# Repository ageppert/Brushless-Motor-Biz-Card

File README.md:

# Brushless-Motor-Biz-Card
Wind your own brushless motor and experiment in the form factor of a business card!

Follow this project at: https://hackaday.io/project/196576-brushless-motor-and-driver-business-card-kit

# Hardware Version History (latest on top)

HWV0.1 - Prototypes

# REFERENCES

Carl Bugeja - PCB Motors and related magical creations

https://www.youtube.com/@CarlBugeja

Random Access Projects - Open loop brushless motor and beyond

https://www.youtube.com/channel/UCRd9x4pmbc09_RXTrkSY2Gg

Electronoobs - brushless motor and ESC projects

https://www.youtube.com/@ELECTRONOOBS

SimpleFOC Project

https://simplefoc.com/

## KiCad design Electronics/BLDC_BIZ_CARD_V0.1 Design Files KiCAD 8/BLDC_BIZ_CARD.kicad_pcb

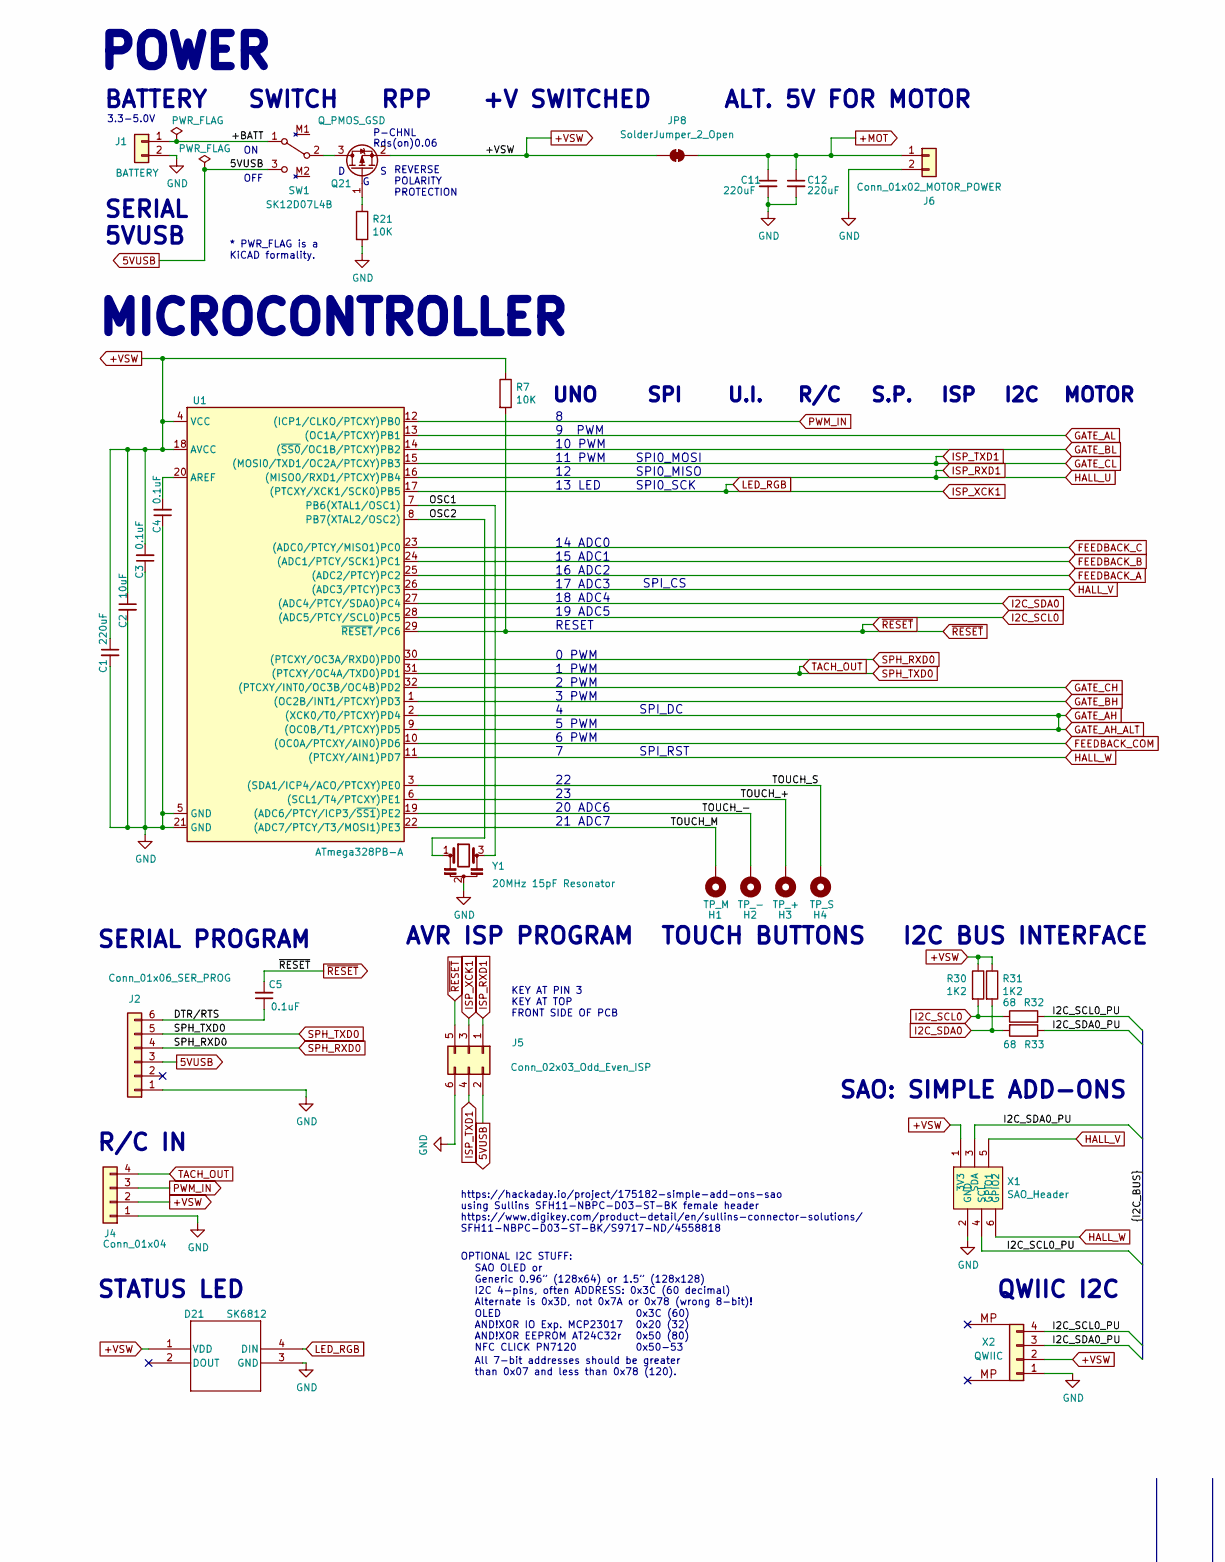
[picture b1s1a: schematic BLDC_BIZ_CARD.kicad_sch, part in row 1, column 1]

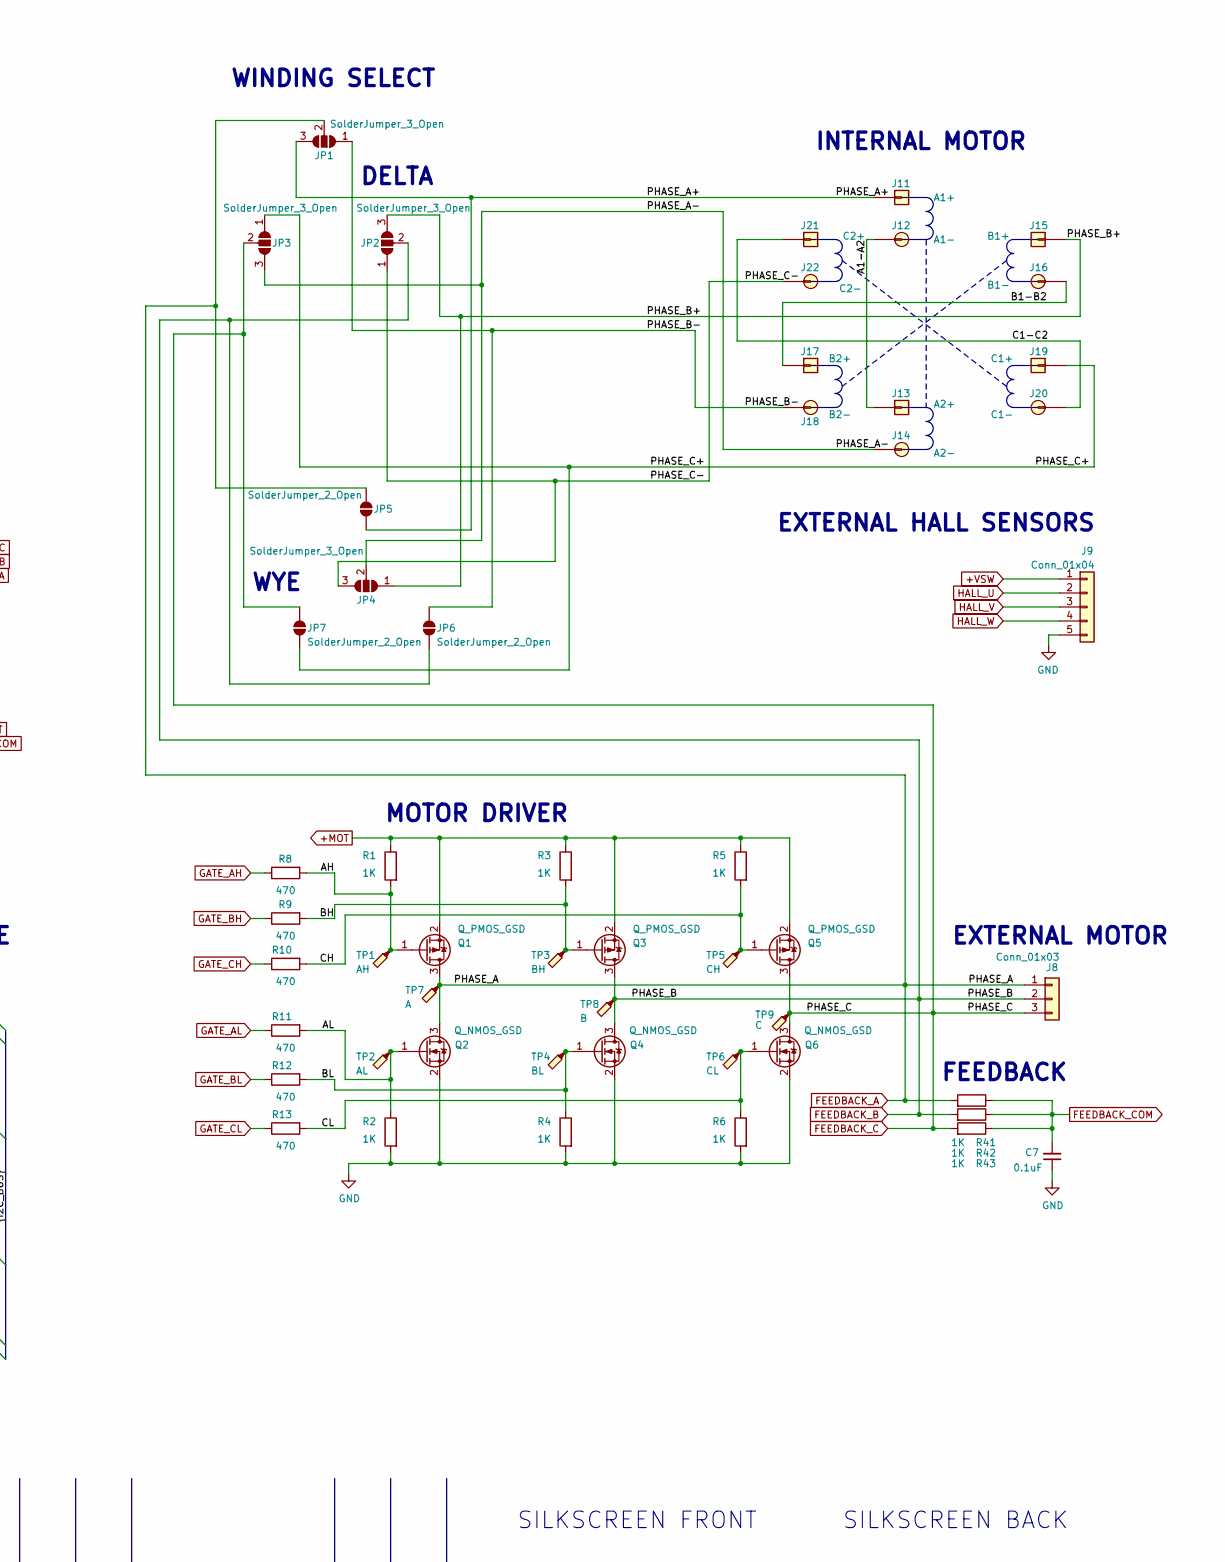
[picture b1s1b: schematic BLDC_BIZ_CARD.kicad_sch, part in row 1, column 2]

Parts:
C1, C11, C12: 220uF; C_1206_3216Metric; LCSC C412252
C2: 10uF; C_0805_2012Metric; LCSC C17024
C3, C4, C5, C7: 0.1uF; C_0805_2012Metric; LCSC C28233
D21: SK6812; 4960_ADA_REV_RGB_LED_short_pads; MPN SK6812-E; Digi-Key_PN 1528-4960-ND
H1: TP_M; BIZ_CARD_TOUCH_PAD
H2: TP_-; BIZ_CARD_TOUCH_PAD
H3: TP_+; BIZ_CARD_TOUCH_PAD
H4: TP_S; BIZ_CARD_TOUCH_PAD
J1: BATTERY; PinSocket_1x02_P2.54mm_Vertical
J2: Conn_01x06_SER_PROG; PinSocket_1x06_P2.54mm_Vertical
J4: Conn_01x04; PinSocket_1x04_P2.54mm_Vertical
J5: Conn_02x03_Odd_Even_ISP; PinSocket_2x03_P2.54mm_Vertical
J6: Conn_01x02_MOTOR_POWER; PinSocket_1x02_P2.54mm_Vertical
J8: Conn_01x03; PinSocket_1x03_P2.54mm_Vertical
J9: Conn_01x04; PinSocket_1x05_P2.54mm_Vertical
J11: A1+; TestPoint_THTPad_1.0x1.0mm_Drill0.5mm
J12: A1-; TestPoint_THTPad_D1.0mm_Drill0.5mm
J13: A2+; TestPoint_THTPad_1.0x1.0mm_Drill0.5mm
J14: A2-; TestPoint_THTPad_D1.0mm_Drill0.5mm
J15: B1+; TestPoint_THTPad_1.0x1.0mm_Drill0.5mm
J16: B1-; TestPoint_THTPad_D1.0mm_Drill0.5mm
J17: B2+; TestPoint_THTPad_1.0x1.0mm_Drill0.5mm
J18: B2-; TestPoint_THTPad_D1.0mm_Drill0.5mm
J19: C1+; TestPoint_THTPad_1.0x1.0mm_Drill0.5mm
J20: C1-; TestPoint_THTPad_D1.0mm_Drill0.5mm
J21: C2+; TestPoint_THTPad_1.0x1.0mm_Drill0.5mm
J22: C2-; TestPoint_THTPad_D1.0mm_Drill0.5mm
JP1, JP2, JP3, JP4: SolderJumper_3_Open; SolderJumper-3_P1.3mm_Open_RoundedPad1.0x1.5mm_NumberLabels
JP5, JP6, JP7, JP8: SolderJumper_2_Open; SolderJumper-2_P1.3mm_Open_RoundedPad1.0x1.5mm
Q1, Q3, Q5: Q_PMOS_GSD; SOT-23-3; Digi-Key_PN DMP2066LSNDICT-ND
Q2, Q4, Q6: Q_NMOS_GSD; SOT-23-3; MPN NVTR4503NT1G; LCSC C20917
Q21: Q_PMOS_GSD; SOT-23-3; MPN SL3401A-TP; LCSC C350311
R1, R2, R3, R4, R5, R6, R41, R42, R43: 1K; R_0805_2012Metric; LCSC C17379
R7, R21: 10K; R_0805_2012Metric; LCSC C269724
R8, R9, R10, R11, R12, R13: 470; R_0805_2012Metric; LCSC C17379
R30, R31: 1K2; R_0805_2012Metric; LCSC C17379
R32, R33: 68; R_0805_2012Metric; LCSC C17802
SW1: SK12D07L4B; SK12D07VG4; MPN OS102011MA1QN1; LCSC C480340
TP1: AH; TestPoint_THTPad_D1.5mm_Drill1.0mm
TP2: AL; TestPoint_THTPad_D1.5mm_Drill1.0mm
TP3: BH; TestPoint_THTPad_D1.5mm_Drill1.0mm
TP4: BL; TestPoint_THTPad_D1.5mm_Drill1.0mm
TP5: CH; TestPoint_THTPad_D1.5mm_Drill1.0mm
TP6: CL; TestPoint_THTPad_D1.5mm_Drill1.0mm
TP7: A; TestPoint_THTPad_D1.5mm_Drill1.0mm
TP8: B; TestPoint_THTPad_D1.5mm_Drill1.0mm
TP9: C; TestPoint_THTPad_D1.5mm_Drill1.0mm
U1: ATmega328PB-A; TQFP-32_7x7mm_P0.8mm; LCSC C132230
X1: SAO_Header; Badgelife-SAOv169-BADGE-2x3; MPN SFH11-NBPC-D03-ST-BK; Digi-Key_PN S9717-ND
X2: QWIIC; JST_SH_SM04B-SRSS-TB_1x04-1MP_P1.00mm_Horizontal; MPN SM04B-SRSS-TB; LCSC C160404
Y1: 20MHz 15pF Resonator; OSC_CSTNE20M0V53Z000R0; LCSC C32180

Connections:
5VUSB: J2.3, J5.2, SW1.3 (C)
+MOT: C11.1, C12.1, J6.1, JP8.1 (A), Q1.2 (S), Q3.2 (S), Q5.2 (S), R1.1, R3.1, R5.1
+VSW: C1.1, C2.1, C3.2, D21.1 (VDD), J4.2, J9.1, JP8.2 (B), Q21.2 (S), R7.1, R30.1, R31.1, U1.4 (VCC), U1.18 (AVCC), X1.1 (3V3), X2.2
/+BATT: J1.1, SW1.1 (A)
/A1-A2: J12.1, J13.1
/AH: Q1.1 (G), R1.2, R8.2, TP1.1
/AL: Q2.1 (G), R2.1, R11.2, TP2.1
/B1-B2: J16.1, J17.1
/BH: Q3.1 (G), R3.2, R9.2, TP3.1
/BL: Q4.1 (G), R4.1, R12.2, TP4.1
/C1-C2: J20.1, J21.1
/CH: Q5.1 (G), R5.2, R10.2, TP5.1
/CL: Q6.1 (G), R6.1, R13.2, TP6.1
/DTR/RTS: C5.1, J2.6
/I2C_SCL0_PU: R32.2, X1.4 (SCL), X2.4
/I2C_SDA0_PU: R33.1, X1.3 (SDA), X2.3
/OSC1: U1.7 (PB6(XTAL1/OSC1)), Y1.3
/OSC2: U1.8 (PB7(XTAL2/OSC2)), Y1.1
/PHASE_A+: J11.1, JP1.3 (B), JP5.1 (A)
/PHASE_A-: J14.1, JP3.3 (B), JP4.2 (C)
/PHASE_B+: J15.1, JP2.3 (B), JP4.1 (A)
/PHASE_B-: J18.1, JP1.1 (A), JP6.2 (B)
/PHASE_C+: J19.1, JP3.1 (A), JP7.1 (A)
/PHASE_C-: J22.1, JP2.1 (A), JP4.3 (B)
/TOUCH_+: H3.1, U1.6 ((SCL1/T4/PTCXY)PE1)
/TOUCH_-: H2.1, U1.19 ((ADC6/PTCY/ICP3/~SS1)PE2)
/TOUCH_M: H1.1, U1.22 ((ADC7/PTCY/T3/MOSI1)PE3)
/TOUCH_S: H4.1, U1.3 ((SDA1/ICP4/ACO/PTCXY)PE0)
FEEDBACK_A: J8.1, JP1.2 (C), JP5.2 (B), Q1.3 (D), Q2.3 (D), R41.2, TP7.1, U1.25 ((ADC2/PTCY)PC2)
FEEDBACK_B: J8.2, JP2.2 (C), JP6.1 (A), Q3.3 (D), Q4.3 (D), R42.2, TP8.1, U1.24 ((ADC1/PTCY/SCK1)PC1)
FEEDBACK_C: J8.3, JP3.2 (C), JP7.2 (B), Q5.3 (D), Q6.3 (D), R43.2, TP9.1, U1.23 ((ADC0/PTCY/MISO1)PC0)
FEEDBACK_COM: C7.2, R41.1, R42.1, R43.1, U1.10 ((OC0A/PTCXY/AIN0)PD6)
GATE_AH: R8.1, U1.2 ((XCK0/T0/PTCXY)PD4), U1.9 ((OC0B/T1/PTCXY)PD5)
GATE_AL: R11.1, U1.13 ((OC1A/PTCXY)PB1)
GATE_BH: R9.1, U1.1 ((OC2B/INT1/PTCXY)PD3)
GATE_BL: R12.1, U1.14 ((~SS0/OC1B/PTCXY)PB2)
GATE_CH: R10.1, U1.32 ((PTCXY/INT0/OC3B/OC4B)PD2)
GATE_CL: J5.4, R13.1, U1.15 ((MOSI0/TXD1/OC2A/PTCXY)PB3)
GND: C1.2, C2.2, C3.1, C4.1, C7.1, C11.2, C12.2, D21.3 (GND), J1.2, J2.1, J4.1, J5.6, J6.2, J9.5, Q2.2 (S), Q4.2 (S), Q6.2 (S), R2.2, R4.2, R6.2, R21.2, U1.5 (GND), U1.21 (GND), X1.2 (GND), X2.1, Y1.2
HALL_U: J5.1, J9.2, U1.16 ((MISO0/RXD1/PTCXY)PB4)
HALL_V: J9.3, U1.26 ((ADC3/PTCY)PC3), X1.5 (GPIO1)
HALL_W: J9.4, U1.11 ((PTCXY/AIN1)PD7), X1.6 (GPIO2)
I2C_SCL0: R30.2, R32.1, U1.28 ((ADC5/PTCY/SCL0)PC5)
I2C_SDA0: R31.2, R33.2, U1.27 ((ADC4/PTCY/SDA0)PC4)
ISP_XCK1: D21.4 (DIN), J5.3, U1.17 ((PTCXY/XCK1/SCK0)PB5)
unnamed: Q21.3 (D), SW1.2 (B)
unnamed: Q21.1 (G), R21.1
unnamed: C4.2, U1.20 (AREF)
PWM_IN: J4.3, U1.12 ((ICP1/CLKO/PTCXY)PB0)
SPH_RXD0: J2.4, U1.30 ((PTCXY/OC3A/RXD0)PD0)
SPH_TXD0: J2.5, J4.4, U1.31 ((PTCXY/OC4A/TXD0)PD1)
~RESET: C5.2, J5.5, R7.2, U1.29 (~RESET/PC6)

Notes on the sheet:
SILKSCREEN FRONT
OLED AND!XOR IO Exp. MCP23017 AND!XOR EEPROM AT24C32r NFC CLICK PN7120
P-CHNL
WYE
EXTERNAL MOTOR
https://hackaday.io/project/175182-simple-add-ons-sao using Sullins SFH11-NBPC-D03-ST-BK female header https://www.digikey.com/product-detail/en/sullins-connector-solutions/ SFH11-NBPC-D03-ST-BK/S9717-ND/4558818
SAO: SIMPLE ADD-ONS
MOTOR
SPI_RST
R/C
AVR ISP PROGRAM
MICROCONTROLLER
0 PWM 1 PWM 2 PWM 3 PWM 4 5 PWM 6 PWM 7
I2C
WINDING SELECT
22 23 20 ADC6 21 ADC7
OFF
UNO
* PWR_FLAG is a KiCAD formality.
SWITCH
DELTA
SAO OLED or Generic 0.96” (128x64) or 1.5” (128x128) I2C 4-pins, often ADDRESS: 0x3C (60 decimal) Alternate is 0x3D, not 0x7A or 0x78 (wrong 8-bit)!
POWER
SPI0_MOSI SPI0_MISO SPI0_SCK
ALT. 5V FOR MOTOR
REVERSE POLARITY PROTECTION
MOTOR DRIVER
U.I.
ISP
SERIAL PROGRAM
Rds(on)0.06
RPP
SPI_DC
8 9 PWM 10 PWM 11 PWM 12 13 LED
S.P.
STATUS LED
KEY AT PIN 3 KEY AT TOP FRONT SIDE OF PCB
BATTERY
SPI
SPI_CS

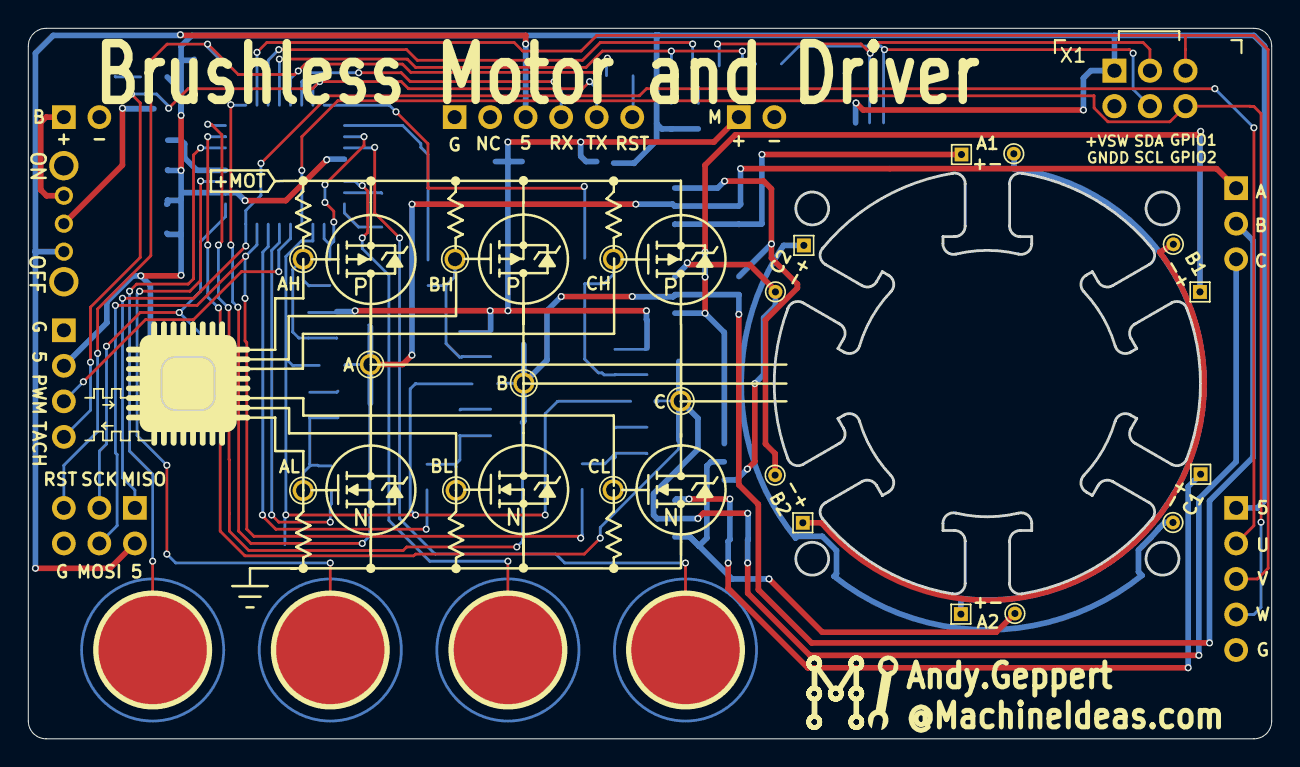
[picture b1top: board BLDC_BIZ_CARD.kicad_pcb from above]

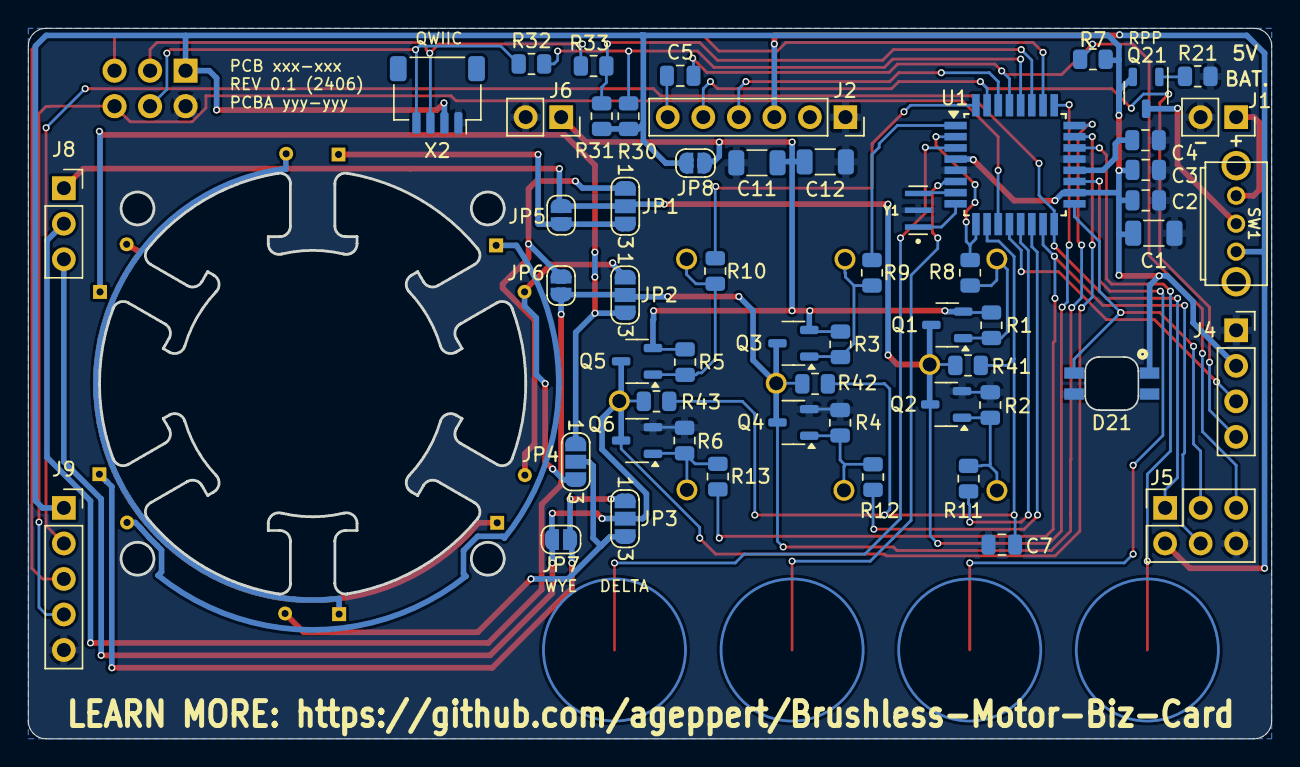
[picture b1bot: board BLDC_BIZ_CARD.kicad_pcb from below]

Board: 2 copper layers, 88.8 x 50.7 mm, 82 parts (55 on the bottom side), 52 nets.

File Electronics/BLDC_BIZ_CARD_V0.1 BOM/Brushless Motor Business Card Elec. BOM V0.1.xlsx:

Brushless Motor and Driver Business Card
Designed by Andy Geppert, www.MachineIdeas.com
Revision 0.1
REF. DES. | VALUE | FOOTPRINT | QUANTITY | DNP | DIGIKEY PN | MFR PN | OTHER
> C1, C11, C12 | 220uF | Capacitor_SMD:C_1206_3216Metric | 3 |  | 490-13970-1-ND | GRM31CR60J227ME11L
C2 | 10uF | Capacitor_SMD:C_0805_2012Metric | 1 |  | 1276-6472-1-ND | CL21B106KOQNNNG
> C3-C5, C7 | 0.1uF | Capacitor_SMD:C_0805_2012Metric | 4 |  | 1276-2922-1-ND | CL21B104KAFNNNE
D21 | SK6812 | Core_64_footprints:4960_ADA_REV_RGB_LED_short_pads | 1 |  | 1528-4960-ND | SK6812-E
J1 | BATTERY | Connector_PinSocket_2.54mm:PinSocket_1x02_P2.54mm_Vertical | 1 |  | See OTHER |  | Any 0.1" header pins such as: https://www.amazon.com/Header-Lystaii-Pin-Connect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
J2 | Conn_01x06_SER_PROG | Connector_PinSocket_2.54mm:PinSocket_1x06_P2.54mm_Vertical | 1 |  | See OTHER
> J4, J9 | Conn_01x04 | -- mixed values -- | 2 |  | See OTHER
J5 | Conn_02x03_Odd_Even_ISP | Connector_PinSocket_2.54mm:PinSocket_2x03_P2.54mm_Vertical | 1 |  | See OTHER
J6 | Conn_01x02_MOTOR_POWER | Connector_PinSocket_2.54mm:PinSocket_1x02_P2.54mm_Vertical | 1 |  | See OTHER
J8 | Conn_01x03 | Connector_PinSocket_2.54mm:PinSocket_1x03_P2.54mm_Vertical | 1 |  | See OTHER
> Q1, Q3, Q5, Q21 | Q_PMOS_GSD | Package_TO_SOT_SMD:SOT-23-3 | 4 |  | DMP2066LSNDICT-ND | DMP2066LSN-7
> Q2, Q4, Q6 | Q_NMOS_GSD | Package_TO_SOT_SMD:SOT-23-3 | 3 |  | DMN2020LSN-7DICT-ND | DMN2020LSN-7
> R1-R6, R41-R43 | 1K | Resistor_SMD:R_0805_2012Metric | 9 |  | 2019-RK73H2ATTD1001FCT-ND | RK73H2ATTD1001F
> R7, R21 | 10K | Resistor_SMD:R_0805_2012Metric | 2 |  | 2019-RK73H2ATTD1002FCT-ND | RK73H2ATTD1002F
> R8-R13 | 470 | Resistor_SMD:R_0805_2012Metric | 6 |  | 2019-RK73H2ATTD4700FCT-ND | RK73H2ATTD4700F
> R30, R31 | 1K2 | Resistor_SMD:R_0805_2012Metric | 2 |  | 2019-RK73H2ATTD1201FCT-ND | RK73H2ATTD1201F
> R32, R33 | 68 | Resistor_SMD:R_0805_2012Metric | 2 |  | 2019-RK73H2ATTD68R0FCT-ND | RK73H2ATTD68R0F
SW1 | SK12D07L4B | BLDC_BIZ_CARD_Footprints:SK12D07VG4 | 1 |  | CKN9559-ND | OS102011MA1QN1
U1 | ATmega328PB-A | Package_QFP:TQFP-32_7x7mm_P0.8mm | 1 |  | ATMEGA328PB-AU-ND | ATMEGA328PB-AU
X1 | SAO_Header | BLDC_BIZ_CARD_Footprints:Badgelife-SAOv169-BADGE-2x3 | 1 |  | S9717-ND | SFH11-NBPC-D03-ST-BK
X2 | QWIIC | Connector_JST:JST_SH_SM04B-SRSS-TB_1x04-1MP_P1.00mm_Horizontal | 1 |  | 455-SM04B-SRSS-TBTR-ND | SM04B-SRSS-TB
Y1 | 16MHz 15pF Resonator | BLDC_BIZ_CARD_Footprints:OSC_CSTNE20M0V53Z000R0 | 1 |  | 490-17950-1-ND | CSTNE16M0V53Z000R0

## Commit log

2024-06-24 Clean out unneeded files
2024-06-29 Rotate ISP port on schematic to match board orientation.
2024-06-29 Twinkle RGB LED and serial port test
2024-06-29 Working I2C and SAO OLED!
2024-06-29 More inspiration link to Carl Bugeja
2024-06-29 Add LED color modes
    LED Green at start-up. LED Blue during OLED set-up. LED blinking RED whilst looping open loop motor control.
2024-06-29 Increase start-up LED color durations, add schematic OLED note
2024-06-30 Implement A-B phase alternate ramp up and down
2024-06-30 Add sine wave test AB positive polarity
2024-06-30 PWMing the high sides too
2024-07-01 It works with 3 blind sine waves!
2024-07-01 Create LICENSE
2024-07-02 Add Mech. and Elec. BOMs
2024-07-02 Increase frequency, refine timing math
    Increase all phases to 32kHz, affects DELAY().
    Add math to auto-calculate starting phase positions from degrees.
    Remove DigitalWriteFast use.
2024-08-25 Add touch sensor design guide
2025-10-01 Add mechanical parts STEP and STL files V1
